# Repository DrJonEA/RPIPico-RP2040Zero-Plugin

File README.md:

# RPIPico-RP2040Zero-Plugin
Use a RPI Pico in a RP2040Zero Socket for development purposes.

I love the small footprint of the RP2040Zero for some projects. Working with it in development though is a pain as the SWD ports are not exposed. To get around this I build an adapter board so I could use a Raspberry Pi Pico as a plugin for the RP2040 Zero during development.

Included in this repo is the kikad  files and an example project.

The adapter also has a reset switch on it and three LED. One is permanently on. The other two are connected to GP20 and GP21 via jumpers. So you can choose to conect these or not into the circuit.

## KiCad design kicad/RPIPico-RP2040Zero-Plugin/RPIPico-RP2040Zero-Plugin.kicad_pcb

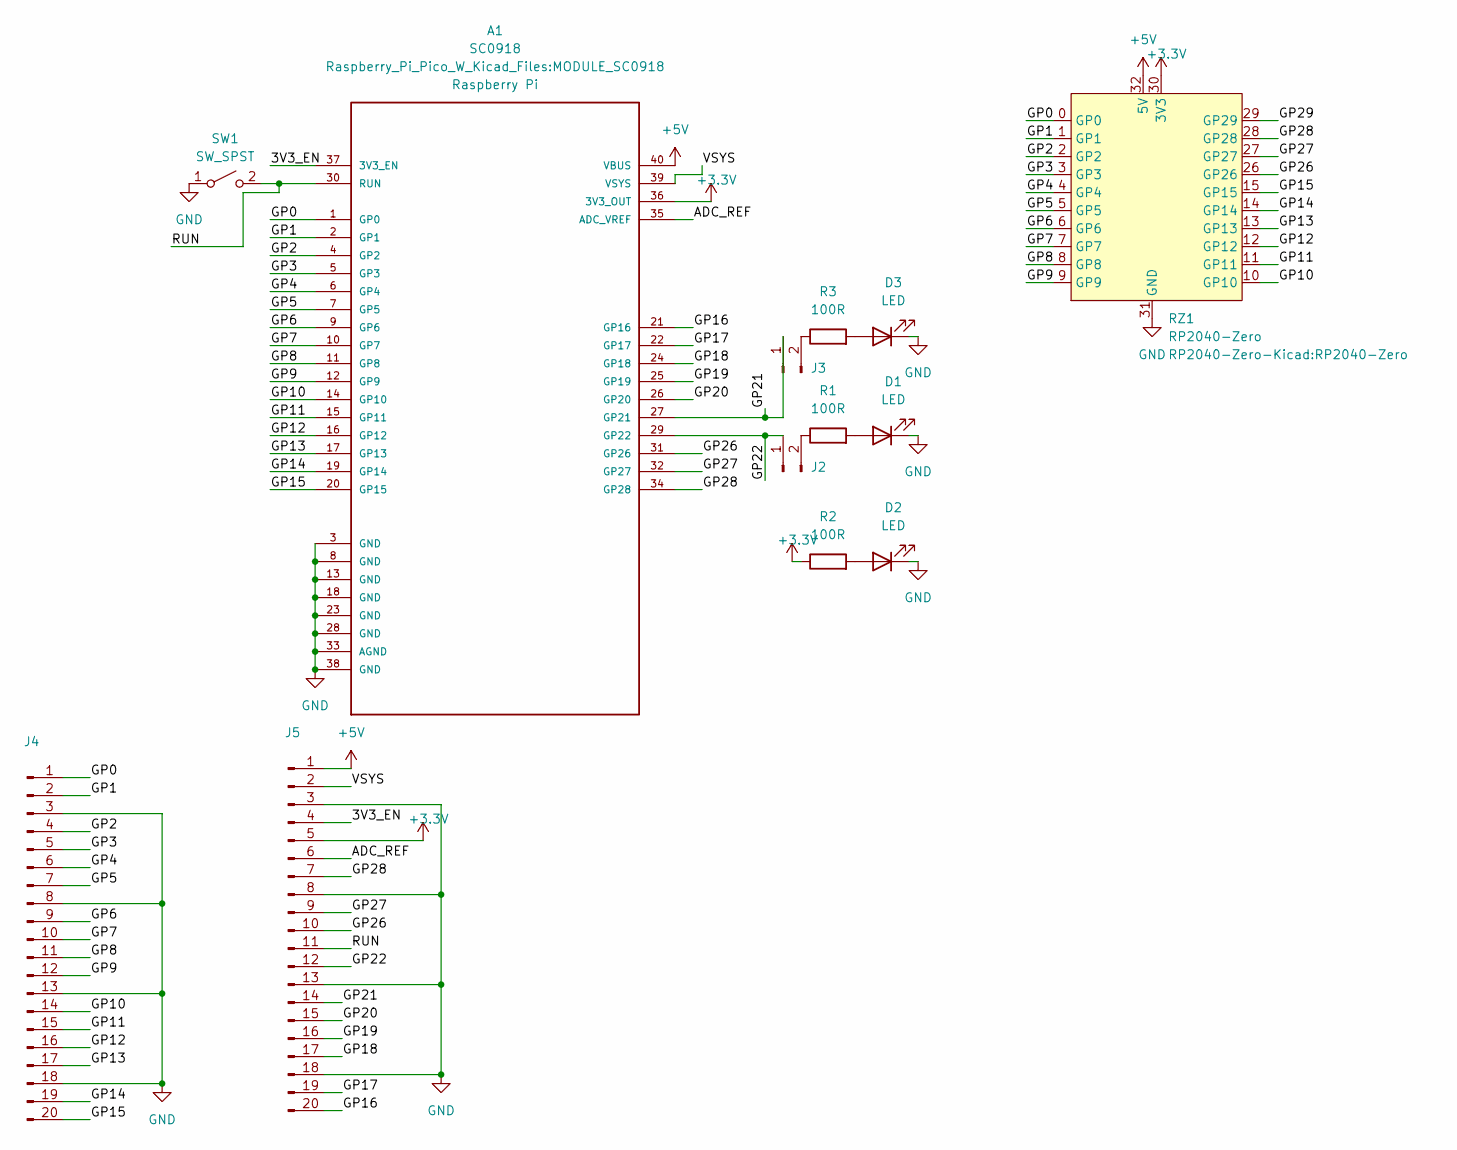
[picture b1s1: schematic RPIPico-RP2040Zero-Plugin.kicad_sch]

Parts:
A1: SC0918; MODULE_SC0918; PARTREV 1.6
D1, D2, D3: LED; LED_D5.0mm
J2, J3: Conn_01x02_Pin; PinHeader_1x02_P2.54mm_Vertical
J4, J5: Conn_01x20_Pin; PinHeader_1x20_P2.54mm_Vertical
R1, R2, R3: 100R; R_Axial_DIN0309_L9.0mm_D3.2mm_P12.70mm_Horizontal
RZ1: RP2040-Zero
SW1: SW_SPST; SW_PUSH_6mm_H8.5mm

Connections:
+3.3V: A1.36 (3V3_OUT), J5.5, R2.1, RZ1.30 (3V3)
+5V: A1.40 (VBUS), J5.1, RZ1.32 (5V)
/3V3_EN: A1.37 (3V3_EN), J5.4
/ADC_REF: A1.35 (ADC_VREF), J5.6
/GP0: A1.1 (GP0), J4.1, RZ1.0 (GP0)
/GP1: A1.2 (GP1), J4.2, RZ1.1 (GP1)
/GP2: A1.4 (GP2), J4.4, RZ1.2 (GP2)
/GP3: A1.5 (GP3), J4.5, RZ1.3 (GP3)
/GP4: A1.6 (GP4), J4.6, RZ1.4 (GP4)
/GP5: A1.7 (GP5), J4.7, RZ1.5 (GP5)
/GP6: A1.9 (GP6), J4.9, RZ1.6 (GP6)
/GP7: A1.10 (GP7), J4.10, RZ1.7 (GP7)
/GP8: A1.11 (GP8), J4.11, RZ1.8 (GP8)
/GP9: A1.12 (GP9), J4.12, RZ1.9 (GP9)
/GP10: A1.14 (GP10), J4.14, RZ1.10 (GP10)
/GP11: A1.15 (GP11), J4.15, RZ1.11 (GP11)
/GP12: A1.16 (GP12), J4.16, RZ1.12 (GP12)
/GP13: A1.17 (GP13), J4.17, RZ1.13 (GP13)
/GP14: A1.19 (GP14), J4.19, RZ1.14 (GP14)
/GP15: A1.20 (GP15), J4.20, RZ1.15 (GP15)
/GP16: A1.21 (GP16), J5.20
/GP17: A1.22 (GP17), J5.19
/GP18: A1.24 (GP18), J5.17
/GP19: A1.25 (GP19), J5.16
/GP20: A1.26 (GP20), J5.15
/GP21: A1.27 (GP21), J3.1, J5.14
/GP22: A1.29 (GP22), J2.1, J5.12
/GP26: A1.31 (GP26), J5.10, RZ1.26 (GP26)
/GP27: A1.32 (GP27), J5.9, RZ1.27 (GP27)
/GP28: A1.34 (GP28), J5.7, RZ1.28 (GP28)
/GP29: RZ1.29 (GP29)
/RUN: A1.30 (RUN), J5.11, SW1.2 (B)
/VSYS: A1.39 (VSYS), J5.2
GND: A1.3 (GND), A1.8 (GND), A1.13 (GND), A1.18 (GND), A1.23 (GND), A1.28 (GND), A1.33 (AGND), A1.38 (GND), D1.1 (K), D2.1 (K), D3.1 (K), J4.3, J4.8, J4.13, J4.18, J5.3, J5.8, J5.13, J5.18, RZ1.31 (GND), SW1.1 (A)
unnamed: D1.2 (A), R1.2
unnamed: D2.2 (A), R2.2
unnamed: D3.2 (A), R3.2
unnamed: J2.2, R1.1
unnamed: J3.2, R3.1

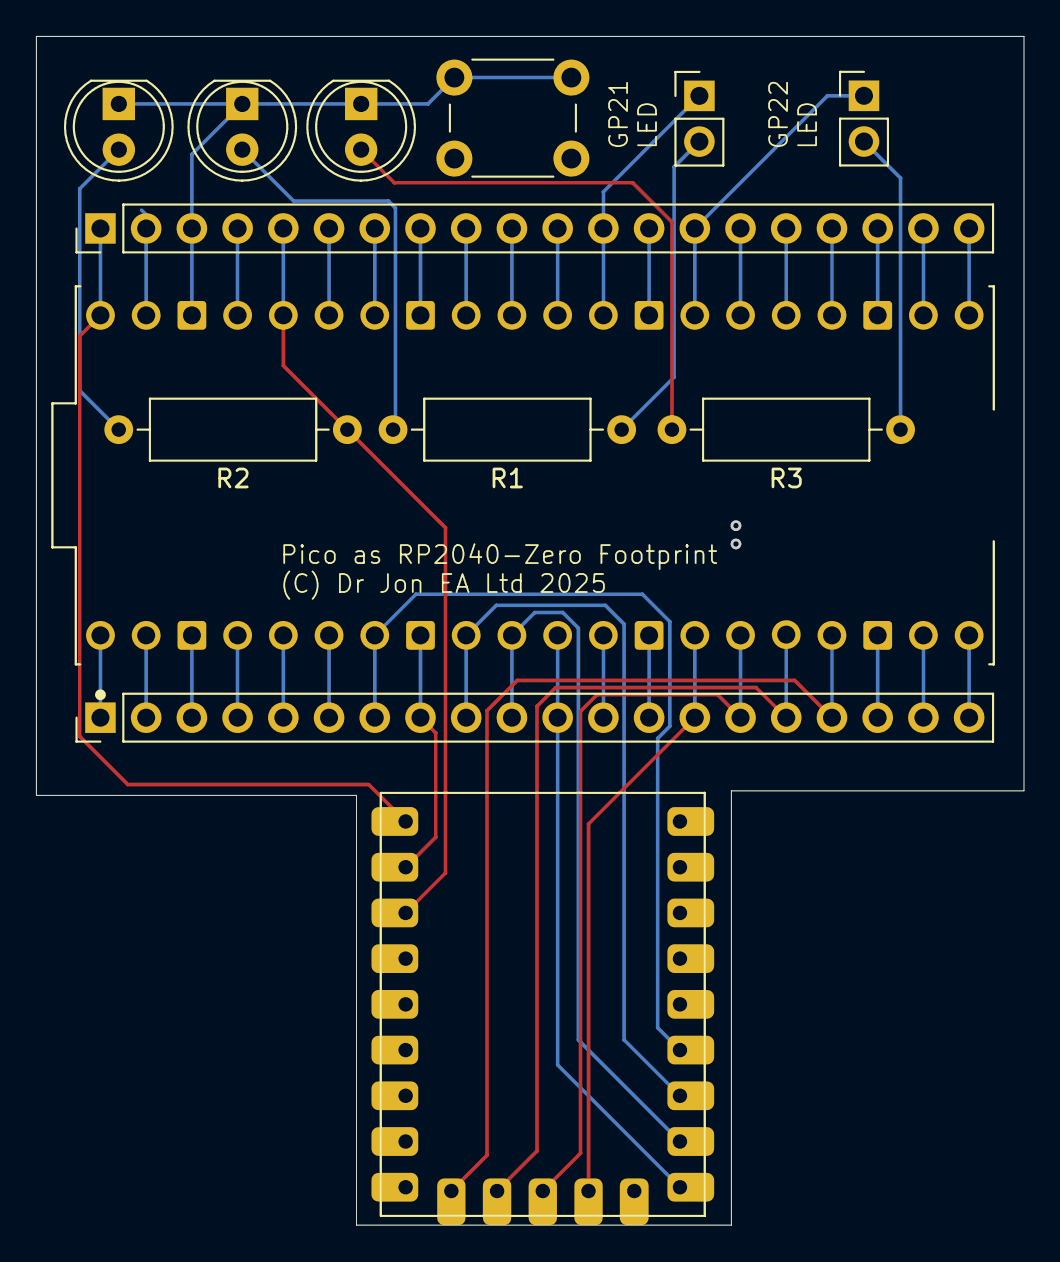
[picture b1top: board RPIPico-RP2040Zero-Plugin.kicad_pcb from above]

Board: 4 copper layers, 54.9 x 66.0 mm, 13 parts (0 on the bottom side), 38 nets.

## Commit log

2025-01-25 initial version
